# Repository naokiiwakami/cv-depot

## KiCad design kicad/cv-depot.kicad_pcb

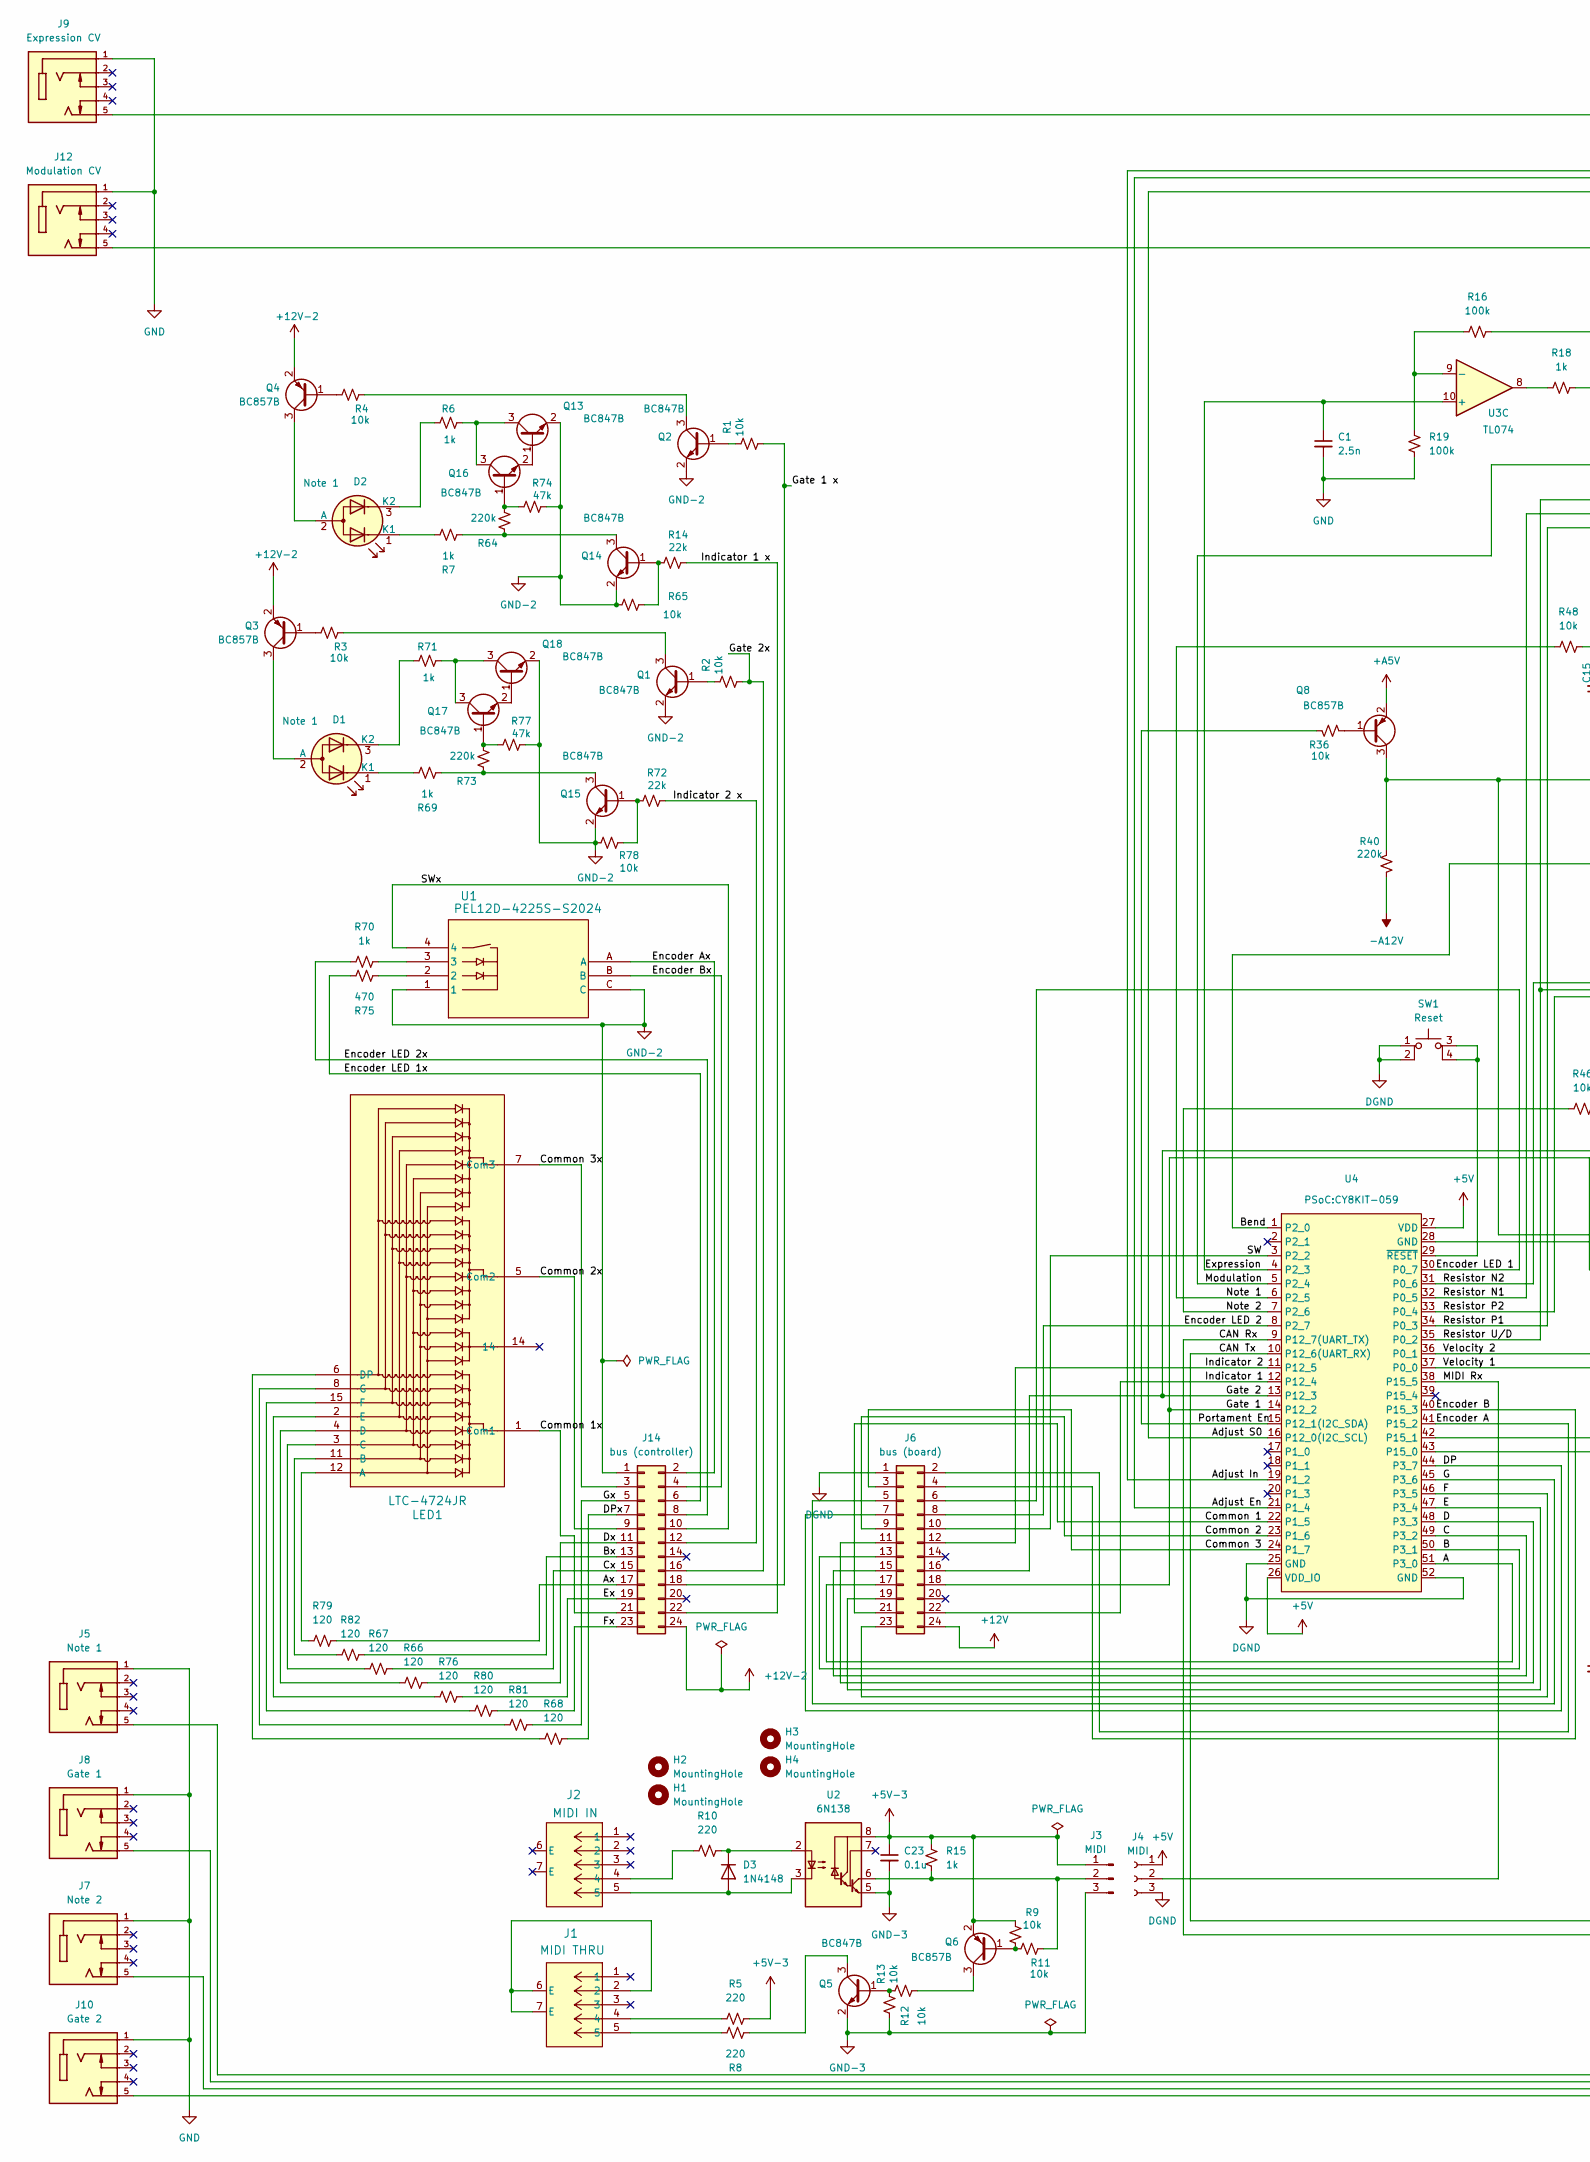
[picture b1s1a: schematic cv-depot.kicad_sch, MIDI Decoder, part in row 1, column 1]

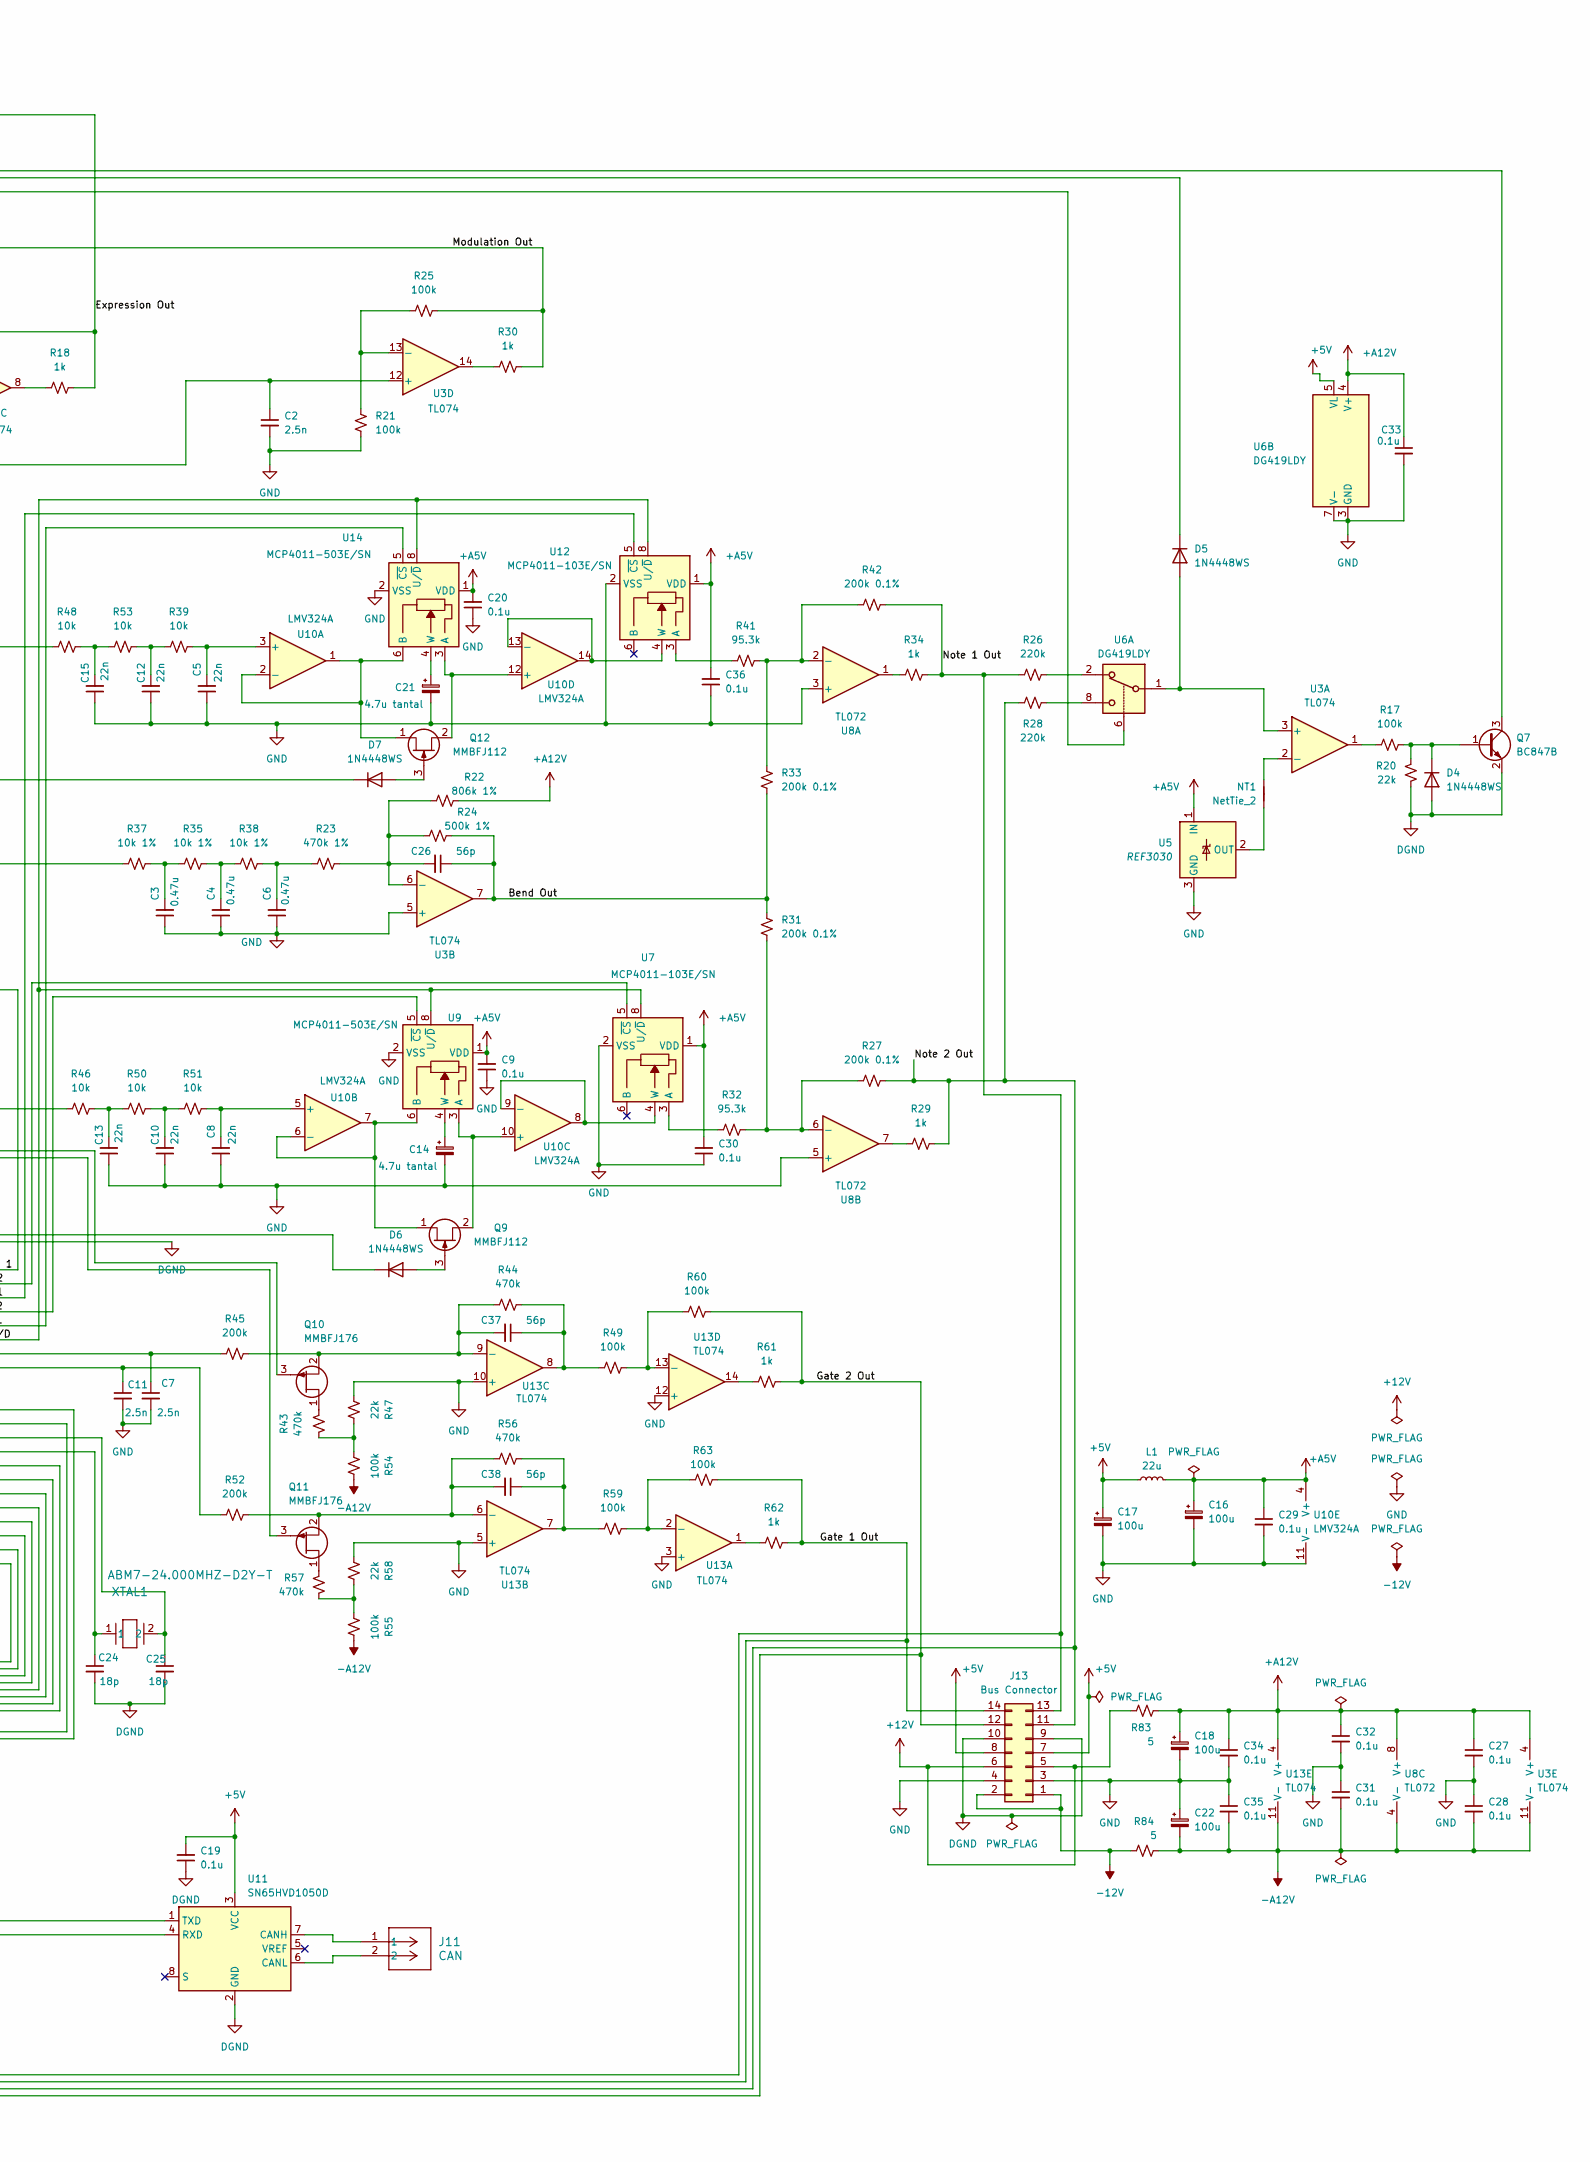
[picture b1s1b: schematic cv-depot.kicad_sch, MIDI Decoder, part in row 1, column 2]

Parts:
C1, C2, C7, C11: 2.5n; C_0805_2012Metric_Pad1.18x1.45mm_HandSolder
C3, C4, C6: 0.47u; C_0805_2012Metric_Pad1.18x1.45mm_HandSolder
C5, C8, C10, C12, C13, C15: 22n; C_0805_2012Metric_Pad1.18x1.45mm_HandSolder
C9, C19, C20, C27, C28, C29, C30, C31, C32, C33, C34, C35, C36: 0.1u; C_0805_2012Metric_Pad1.18x1.45mm_HandSolder
C14, C21: 4.7u tantal; CP_EIA-3216-10_Kemet-I_Pad1.58x1.35mm_HandSolder
C16, C17: 100u; CP_Elec_5x5.3
C18, C22: 100u; CP_Radial_D6.3mm_P2.50mm
C23: 0.1u; R_0805_2012Metric_Pad1.20x1.40mm_HandSolder
C24, C25: 18p; C_0805_2012Metric_Pad1.18x1.45mm_HandSolder
C26, C37, C38: 56p; C_0805_2012Metric_Pad1.18x1.45mm_HandSolder
D1, D2: Note 1; LED_D5.0mm-3
D3: 1N4148; D_DO-35_SOD27_P7.62mm_Horizontal
D4, D5, D6, D7: 1N4448WS; D_SOD-323_HandSoldering
H1, H2, H3, H4: MountingHole; MountingHole_3.2mm_M3
J1: MIDI THRU; CONN5_SDS-50J_CUD
J2: MIDI IN; CONN5_SDS-50J_CUD
J3: MIDI; PinHeader_1x03_P2.54mm_Vertical
J4: MIDI; PinSocket_1x03_P2.54mm_Vertical
J5: Note 1; CONN_35RAPC4BH3_SWC; PARTREV J
J6: bus (board); PinHeader_2x12_P2.54mm_Vertical
J7: Note 2; CONN_35RAPC4BH3_SWC; PARTREV J
J8: Gate 1; CONN_35RAPC4BH3_SWC; PARTREV J
J9: Expression CV; CONN_35RAPC4BH3_SWC; PARTREV J
J10: Gate 2; CONN_35RAPC4BH3_SWC; PARTREV J
J11: CAN; CONN_A-6373-02A_MOL
J12: Modulation CV; CONN_35RAPC4BH3_SWC; PARTREV J
J13: Bus Connector; IDC-Header_2x07_P2.54mm_Vertical
J14: bus (controller); PinHeader_2x12_P2.54mm_Vertical
L1: 22u; L_0805_2012Metric_Pad1.05x1.20mm_HandSolder
LED1: LTC-4724JR; LTC-4724JR_LTO
NT1: NetTie_2; NetTie-2_SMD_Pad0.5mm
Q1, Q2, Q5, Q7, Q13, Q14, Q15, Q16, Q17, Q18: BC847B; SOT-23
Q3, Q4, Q6, Q8: BC857B; SOT-23
Q9, Q12: MMBFJ112; SOT-23
Q10, Q11: MMBFJ176; SOT-23
R1, R2, R3, R4, R9, R11, R12, R13, R36, R39, R46, R48, R50, R51, R53, R65, R78: 10k; D_0805_2012Metric_Pad1.15x1.40mm_HandSolder
R5, R8, R10: 220; R_0805_2012Metric_Pad1.20x1.40mm_HandSolder
R6, R7, R18, R29, R30, R34, R61, R62, R69, R70, R71: 1k; D_0805_2012Metric_Pad1.15x1.40mm_HandSolder
R14, R20, R72: 22k; D_0805_2012Metric_Pad1.15x1.40mm_HandSolder
R15: 1k; R_0805_2012Metric_Pad1.20x1.40mm_HandSolder
R16, R17, R19, R21, R25: 100k; D_0805_2012Metric_Pad1.15x1.40mm_HandSolder
R22: 806k 1%; D_0805_2012Metric_Pad1.15x1.40mm_HandSolder
R23: 470k 1%; D_0805_2012Metric_Pad1.15x1.40mm_HandSolder
R24: 500k 1%; D_0805_2012Metric_Pad1.15x1.40mm_HandSolder
R26, R28, R40, R64, R73: 220k; D_0805_2012Metric_Pad1.15x1.40mm_HandSolder
R27, R31, R33: 200k 0.1%; R_0805_2012Metric_Pad1.20x1.40mm_HandSolder
R32, R41: 95.3k; R_0805_2012Metric_Pad1.20x1.40mm_HandSolder
R35, R37, R38: 10k 1%; D_0805_2012Metric_Pad1.15x1.40mm_HandSolder
R42: 200k 0.1%; D_0805_2012Metric_Pad1.15x1.40mm_HandSolder
R43, R44, R56, R57: 470k; R_0805_2012Metric_Pad1.20x1.40mm_HandSolder
R45, R52: 200k; R_0805_2012Metric_Pad1.20x1.40mm_HandSolder
R47, R58: 22k; R_0805_2012Metric_Pad1.20x1.40mm_HandSolder
R49, R54, R55, R59, R60, R63: 100k; R_0805_2012Metric_Pad1.20x1.40mm_HandSolder
R66, R67, R68, R76, R79, R80, R81, R82: 120; R_0805_2012Metric_Pad1.20x1.40mm_HandSolder
R74, R77: 47k; D_0805_2012Metric_Pad1.15x1.40mm_HandSolder
R75: 470; D_0805_2012Metric_Pad1.15x1.40mm_HandSolder
R83, R84: 5; R_0805_2012Metric_Pad1.20x1.40mm_HandSolder
SW1: Reset; SW4_1825910-B_TEC
U1: PEL12D-4225S-S2024; TO_4225S-S2024
U2: 6N138; DIP-8_W7.62mm_LongPads
U3, U13: TL074; SOIC-14_3.9x8.7mm_P1.27mm
U4: CY8KIT-059
U5: REF3030; SOT-23
U6: DG419LDY; SOIC-8_3.9x4.9mm_P1.27mm
U7, U12: MCP4011-103E/SN; SOIC-8_3.9x4.9mm_P1.27mm
U8: TL072; SOIC-8_3.9x4.9mm_P1.27mm
U9, U14: MCP4011-503E/SN; SOIC-8_3.9x4.9mm_P1.27mm
U10: LMV324A; SOIC-14_3.9x8.7mm_P1.27mm
U11: SN65HVD1050D; SOIC-8_3.9x4.9mm_P1.27mm
XTAL1: ABM7-24.000MHZ-D2Y-T; XTAL_ABM7_ABR_handsoldering

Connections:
+5V: C17.1, C19.2, J4.1, J13.7, J13.8, L1.1, U4.26 (VDD_IO), U4.27 (VDD), U6.5 (VL), U11.3 (VCC)
+5V-3: C23.1, J3.1, Q6.2 (E), R5.2, R9.2, R15.2, U2.8 (VCC)
+12V: J6.24, J13.5, J13.6, R83.1
+12V-2: J14.24, Q3.2 (E), Q4.2 (E)
+A5V: C9.2, C16.1, C20.2, C29.1, C30.2, C36.2, L1.2, Q8.2 (E), U5.1 (IN), U7.1 (VDD), U9.1 (VDD), U10.4 (V+), U12.1 (VDD), U14.1 (VDD)
+A12V: C18.1, C27.1, C32.1, C33.1, C34.1, R22.2, R83.2, U3.4 (V+), U6.4 (V+), U8.8 (V+), U13.4 (V+)
-12V: J13.1, J13.2, R84.1
-A12V: C22.2, C28.2, C31.2, C35.2, R40.1, R54.2, R55.2, R84.2, U3.11 (V-), U8.4 (V-), U13.11 (V-)
/A: J6.17, U4.51 (P3_0)
/Adjust En: D5.1 (K), U4.21 (P1_4)
/Adjust In: Q7.3 (C), U4.19 (P1_2)
/Adjust S0: U4.16 (P12_0(I2C_SCL)), U6.6
/Ax: J14.17, R79.2
/B: J6.13, U4.50 (P3_1)
/Bend: R37.1, U4.1 (P2_0)
/Bend Out: C26.1, R24.2, R31.2, R33.1, U3.7
/Bx: J14.13, R82.2
/C: J6.15, U4.49 (P3_2)
/CAN Rx: U4.9 (P12_7(UART_TX)), U11.4 (RXD)
/CAN Tx: U4.10 (P12_6(UART_RX)), U11.1 (TXD)
/Common 1: J6.21, U4.22 (P1_5)
/Common 1x: J14.21, LED1.1 (Com1)
/Common 2: J6.9, U4.23 (P1_6)
/Common 2x: J14.9, LED1.5 (Com2)
/Common 3: J6.3, U4.24 (P1_7)
/Common 3x: J14.3, LED1.7 (Com3)
/Cx: J14.15, R67.2
/D: J6.11, U4.48 (P3_3)
/DP: J6.7, U4.44 (P3_7)
/DPx: J14.7, R68.2
/Dx: J14.11, R66.2
/E: J6.19, U4.47 (P3_4)
/Encoder A: J6.2, U4.41 (P15_2)
/Encoder Ax: J14.2, U1.A
/Encoder B: J6.4, U4.40 (P15_3)
/Encoder Bx: J14.4, U1.B
/Encoder LED 1: J6.6, U4.30 (P0_7)
/Encoder LED 1x: J14.6, R75.2
/Encoder LED 2: J6.8, U4.8 (P2_7)
/Encoder LED 2x: J14.8, R70.1
/Ex: J14.19, R76.2
/Expression: C1.1, U3.10 (+), U4.4 (P2_3)
/Expression Out: J9.5, R16.2, R18.2
/F: J6.23, U4.46 (P3_5)
/Fx: J14.23, R80.2
/G: J6.5, U4.45 (P3_6)
/Gate 1: J6.18, Q11.3 (G), U4.14 (P12_2)
/Gate 1 Out: J8.5, J13.14, R62.2, R63.2
/Gate 1 x: J14.18, R1.1
/Gate 2: J6.16, Q10.3 (G), U4.13 (P12_3)
/Gate 2 Out: J10.5, J13.12, R60.2, R61.2
/Gate 2x: J14.16, R2.1
/Gx: J14.5, R81.2
/Indicator 1: J6.22, U4.12 (P12_4)
/Indicator 1 x: J14.22, R14.1
/Indicator 2: J6.12, U4.11 (P12_5)
/Indicator 2 x: J14.12, R72.1
/MIDI Rx: J4.2, U4.38 (P15_5)
/Modulation: C2.1, U3.12 (+), U4.5 (P2_4)
/Modulation Out: J12.5, R25.2, R30.2
/Note 1: R48.1, U4.6 (P2_5)
/Note 1 Out: J5.5, J13.13, R26.1, R34.2, R42.2
/Note 2: R46.1, U4.7 (P2_6)
/Note 2 Out: J7.5, J13.11, R27.2, R28.2, R29.2
/Portament En: R36.2, U4.15 (P12_1(I2C_SDA))
/Resistor N1: U4.32 (P0_5), U12.5 (~CS)
/Resistor N2: U4.31 (P0_6), U7.5 (~CS)
/Resistor P1: U4.34 (P0_3), U14.5 (~CS)
/Resistor P2: U4.33 (P0_4), U9.5 (~CS)
/Resistor U/D: U4.35 (P0_2), U7.8 (U/~D), U9.8 (U/~D), U12.8 (U/~D), U14.8 (U/~D)
/SW: J6.10, U4.3 (P2_2)
/SWx: J14.10, U1.4
/Velocity 1: C11.1, R52.1, U4.37 (P0_0)
/Velocity 2: C7.1, R45.1, U4.36 (P0_1)
DGND: C19.1, C24.2, C25.2, D4.2 (A), J4.3, J6.1, J13.9, J13.10, Q7.2 (E), R20.1, SW1.1, SW1.2, U4.25 (GND), U4.28 (GND), U4.52 (GND), U11.2 (GND)
GND: C1.2, C2.2, C3.1, C4.1, C5.1, C6.1, C7.2, C8.1, C9.1, C10.1, C11.2, C12.1, C13.1, C14.2, C15.1, C16.2, C17.2, C18.2, C20.1, C21.2, C22.1, C27.2, C28.1, C29.2, C30.1, C31.1, C32.2, C33.2, C34.2, C35.1, C36.1, J5.1, J7.1, J8.1, J9.1, J10.1, J12.1, J13.3, J13.4, R19.1, R21.1, R47.1, R58.1, U3.5 (+), U5.3 (GND), U6.3 (GND), U6.7 (V-), U7.2 (VSS), U8.3 (+), U8.5 (+), U9.2 (VSS), U10.11 (V-), U12.2 (VSS), U13.3 (+), U13.5 (+), U13.10 (+), U13.12 (+), U14.2 (VSS)
GND-2: J14.1, Q1.2 (E), Q2.2 (E), Q13.2 (E), Q14.2 (E), Q15.2 (E), Q18.2 (E), R65.2, R74.2, R77.2, R78.2, U1.1, U1.C
GND-3: C23.2, J3.3, Q5.2 (E), R12.2, U2.5 (GND)
unnamed: C3.2, R35.1, R37.2
unnamed: C4.2, R35.2, R38.1
unnamed: C6.2, R23.1, R38.2
unnamed: C10.2, R50.2, R51.1
unnamed: C12.2, R39.1, R53.2
unnamed: C13.2, R46.2, R50.1
unnamed: C15.2, R48.2, R53.1
unnamed: C37.1, R44.2, R49.1, U13.8
unnamed: C38.1, R56.2, R59.1, U13.7
unnamed: D1.2 (A), Q3.3 (C)
unnamed: D1.1 (K1), R69.2
unnamed: D1.3 (K2), R71.1
unnamed: D2.2 (A), Q4.3 (C)
unnamed: D2.1 (K1), R7.2
unnamed: D2.3 (K2), R6.1
unnamed: D3.2 (A), J2.5, U2.3 (C2)
unnamed: D3.1 (K), R10.1, U2.2 (C1)
unnamed: D4.1 (K), Q7.1 (B), R17.2, R20.2
unnamed: D5.2 (A), U3.3 (+), U6.1
unnamed: D6.2 (A), Q9.3 (G)
unnamed: D6.1 (K), D7.1 (K), Q8.3 (C), R40.2
unnamed: D7.2 (A), Q12.3 (G)
unnamed: J1.2, J1.6 (E), J1.7 (E)
unnamed: J1.4, R5.1
unnamed: J1.5, R8.2
unnamed: J2.4, R10.2
unnamed: J3.2, R11.2, R15.1, U2.6 (VO2)
unnamed: LED1.12 (A), R79.1
unnamed: LED1.11 (B), R82.1
unnamed: LED1.3 (C), R67.1
unnamed: LED1.4 (D), R66.1
unnamed: LED1.6 (DP), R68.1
unnamed: LED1.2 (E), R76.1
unnamed: LED1.15 (F), R80.1
unnamed: LED1.8 (G), R81.1
unnamed: Q1.1 (B), R2.2
unnamed: Q1.3 (C), R3.2
unnamed: Q2.1 (B), R1.2
unnamed: Q2.3 (C), R4.2
unnamed: Q3.1 (B), R3.1
unnamed: Q4.1 (B), R4.1
unnamed: Q5.1 (B), R12.1, R13.2
unnamed: Q5.3 (C), R8.1
unnamed: Q6.1 (B), R9.1, R11.1
unnamed: Q6.3 (C), R13.1
unnamed: Q8.1 (B), R36.1
unnamed: Q9.1 (D), U9.6 (B), U10.6 (-), U10.7
unnamed: Q9.2 (S), U9.3 (A), U10.10 (+)
unnamed: Q10.1 (D), R43.1
unnamed: C37.2, Q10.2 (S), R44.1, R45.2, U13.9 (-)
unnamed: Q11.1 (D), R57.1
unnamed: C38.2, Q11.2 (S), R52.2, R56.1, U13.6 (-)
unnamed: Q12.1 (D), U10.1, U10.2 (-), U14.6 (B)
unnamed: Q12.2 (S), U10.12 (+), U14.3 (A)
unnamed: Q13.1 (B), Q16.2 (E)
unnamed: Q13.3 (C), Q16.3 (C), R6.2
unnamed: Q14.1 (B), R14.2, R65.1
unnamed: Q14.3 (C), R7.1, R64.2
unnamed: Q15.1 (B), R72.2, R78.1
unnamed: Q15.3 (C), R69.1, R73.2
unnamed: Q16.1 (B), R64.1, R74.1
unnamed: Q17.1 (B), R73.1, R77.1
unnamed: Q17.3 (C), Q18.3 (C), R71.2
unnamed: Q17.2 (E), Q18.1 (B)
unnamed: R17.1, U3.1
unnamed: R18.1, U3.8
unnamed: R26.2, U6.2
unnamed: R28.1, U6.8
unnamed: R29.1, U8.7
unnamed: R30.1, U3.14
unnamed: R34.1, U8.1
unnamed: R43.2, R47.2, R54.1
unnamed: R55.1, R57.2, R58.2
unnamed: R61.1, U13.14
unnamed: R62.1, U13.1
unnamed: R70.2, U1.3
unnamed: R75.1, U1.2
unnamed: NT1.2, U3.2 (-)
unnamed: C26.2, R22.1, R23.2, R24.1, U3.6 (-)
unnamed: R16.1, R19.2, U3.9 (-)
unnamed: R21.2, R25.1, U3.13 (-)
unnamed: C24.1, U4.43 (P15_0), XTAL1.1
unnamed: C25.1, U4.42 (P15_1), XTAL1.2
unnamed: SW1.3, SW1.4, U4.29 (~RESET)
unnamed: NT1.1, U5.2 (OUT)
unnamed: R32.1, U7.3 (A)
unnamed: R33.2, R41.2, R42.1, U8.2 (-)
unnamed: R27.1, R31.1, R32.2, U8.6 (-)
unnamed: C14.1, U9.4 (W)
unnamed: C5.2, R39.2, U10.3 (+)
unnamed: C8.2, R51.2, U10.5 (+)
unnamed: U7.4 (W), U10.8, U10.9 (-)
unnamed: U10.13 (-), U10.14, U12.4 (W)
unnamed: J11.1, U11.7 (CANH)
unnamed: J11.2, U11.6 (CANL)
unnamed: R41.1, U12.3 (A)
unnamed: R59.2, R63.1, U13.2 (-)
unnamed: R49.2, R60.1, U13.13 (-)
unnamed: C21.1, U14.4 (W)

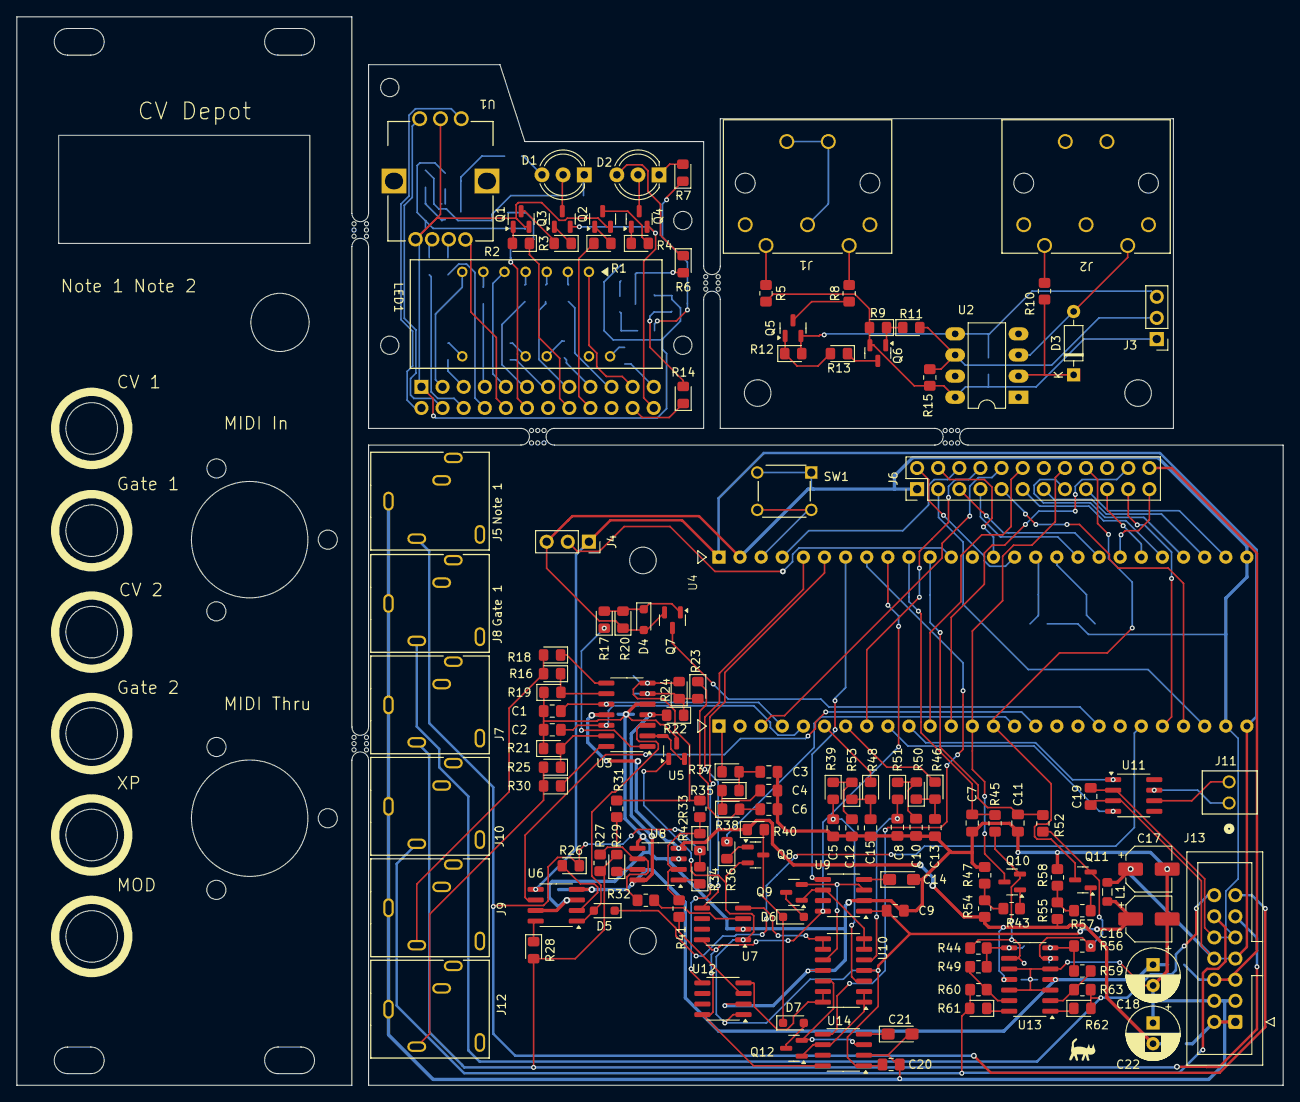
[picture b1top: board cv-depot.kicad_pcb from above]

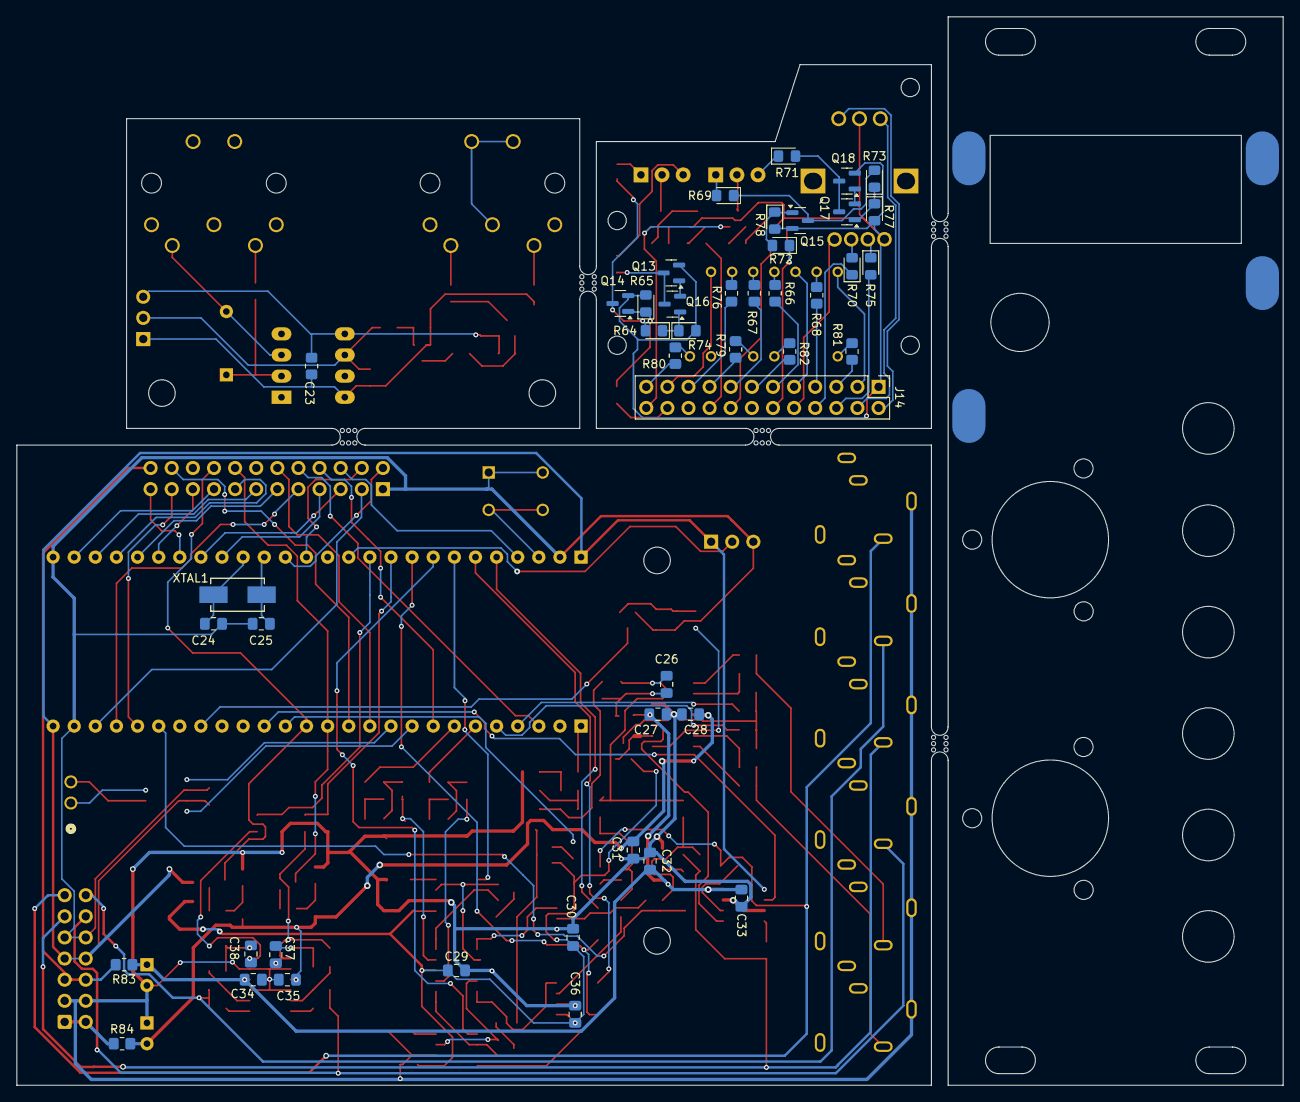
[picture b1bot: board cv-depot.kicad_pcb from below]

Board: 2 copper layers, 152.3 x 128.5 mm, 205 parts (49 on the bottom side), 177 nets.

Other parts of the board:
MB1: MB1; mouse-bite-2mm-slot
MB2: MB2; mouse-bite-2mm-slot
MB3: mb3; mouse-bite-2mm-slot
MB4: MB4; mouse-bite-2mm-slot
MB5: MB5; mouse-bite-2mm-slot
P1, P2: LED Window 5mm
P3: LTC-4724JR_LTO
P4: PEL12D
P5, P6, P8, P9, P10, P11: 3.5mm single channel
P7, P12: DIN 5 pin
P13, P14, P15, P16: Spacer 2M without hole

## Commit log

2025-02-04 Schematics and board initial commit
2025-02-14 revision 1
2025-02-14 renamed KiCad files
2025-02-20 renamed the project again
2025-02-20 tweaked the PCB design
2025-02-20 updated .gitignore file
2025-02-23 put all necessary components to shopping carts
2025-03-31 done with initial hardware check except voltage outputs
2025-04-02 wip: hardware verification
2025-04-02 added digital pot controller, verified in debugger (not yet in full speed)
2025-04-03 add calibration mode, wip
2025-04-04 removed unnecessary _1 suffxies from component names
2025-04-05 established a methodology to move the digital pot wipers
2025-04-05 code cleansing
2025-04-05 bugfix
2025-04-05 fixed issues in pot control
2025-04-06 CV range calibration, wip
2025-04-06 CV range calbration, wip2
2025-04-06 tweaked measurement wait time
2025-04-06 CV range calibration, wip3
2025-04-06 CV range calibration, done
2025-04-20 Checkpoint before refactoring MIDI decoder
2025-04-21 started implementing the key assigner
2025-04-21 Modified the value of the resistor for the green LED
2025-04-23 enabled duophonic
2025-04-24 Start moving MIDI functionality out of main.c
2025-04-25 Moved settings out of main.c
2025-04-26 done with fundamental part of key assignment and MIDI channel setup
2025-04-26 refactoring
2025-04-26 add setting confirmation animation
2025-04-26 fixed issue in handling negative menu index
2025-04-27 refactor - separate implementation dependent part out of key assigner
2025-04-27 improve calibration performance
2025-05-02 Changed gate voltage ranges
2025-05-20 Start adding analog3 message forwarding
2025-05-20 Double the system clock frequency
2025-05-24 Add analog3 module ID assignment
2025-05-30 Start implementing Analog3 message handling
2025-06-01 Add visual option to the ping reply
2025-06-03 add GetName operation support (draft implementation)
2025-06-11 adding get-config operation, wip
2025-06-15 introduced admin wire
2025-06-15 refactor stream control
2025-06-15 Add feature to download config (#1)
2025-06-17 configuration remote setting, wip
2025-06-18 Done with initial implementation of setting config
2025-06-18 New feature: Setting configuration from mission control (#2)
2025-08-23 Improve stability of CAN communication
2025-10-21 Add a new feature - Gate type (Analog3/Legacy)
2025-11-19 Put delays on gate signals
2025-11-27 Bugfix in the key assigner
2025-11-27 Add support for pitch bend
2025-12-04 Add support for expression and modulation
2026-02-02 update the A3 protocol wrt data streaming
